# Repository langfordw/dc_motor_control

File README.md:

# dc_motor_control
microcode for control of DC motors

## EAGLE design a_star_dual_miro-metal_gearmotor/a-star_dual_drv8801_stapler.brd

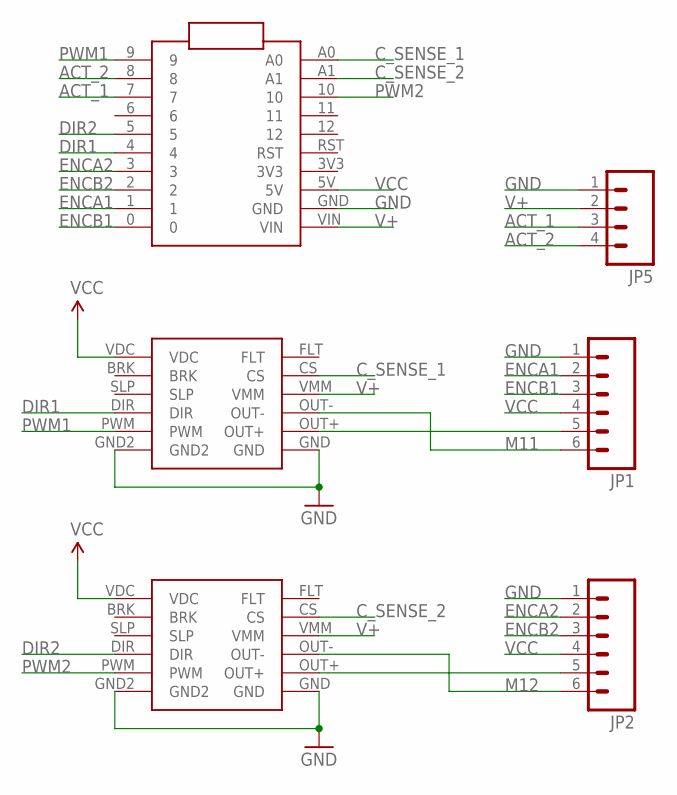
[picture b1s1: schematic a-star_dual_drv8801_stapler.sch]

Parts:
JP1, JP2: M06POLAR; MOLEX-1X6
JP5: M04POLAR; MOLEX-1X4
U$1, U$3: POLOLU_DRV8801_CARRIER
U$2: POLOLU_A-STAR-MICRO

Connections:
ACT_1: JP5.3, U$2.7
ACT_2: JP5.4, U$2.8
C_SENSE_1: U$1.CS, U$2.A0
C_SENSE_2: U$2.A1, U$3.CS
DIR1: U$1.DIR, U$2.4
DIR2: U$2.5, U$3.DIR
ENCA1: JP1.2, U$2.1
ENCA2: JP2.2, U$2.3
ENCB1: JP1.3, U$2.0
ENCB2: JP2.3, U$2.2
GND: JP1.1, JP2.1, JP5.1, U$1.GND, U$1.GND2, U$2.GND, U$3.GND, U$3.GND2
M11: JP1.6, U$1.OUT-
M12: JP2.6, U$3.OUT-
unnamed: JP2.5, U$3.OUT+
unnamed: JP1.5, U$1.OUT+
PWM1: U$1.PWM, U$2.9
PWM2: U$2.10, U$3.PWM
V+: JP5.2, U$1.VMM, U$2.VIN, U$3.VMM
VCC: JP1.4, JP2.4, U$1.VDC, U$2.5V, U$3.VDC

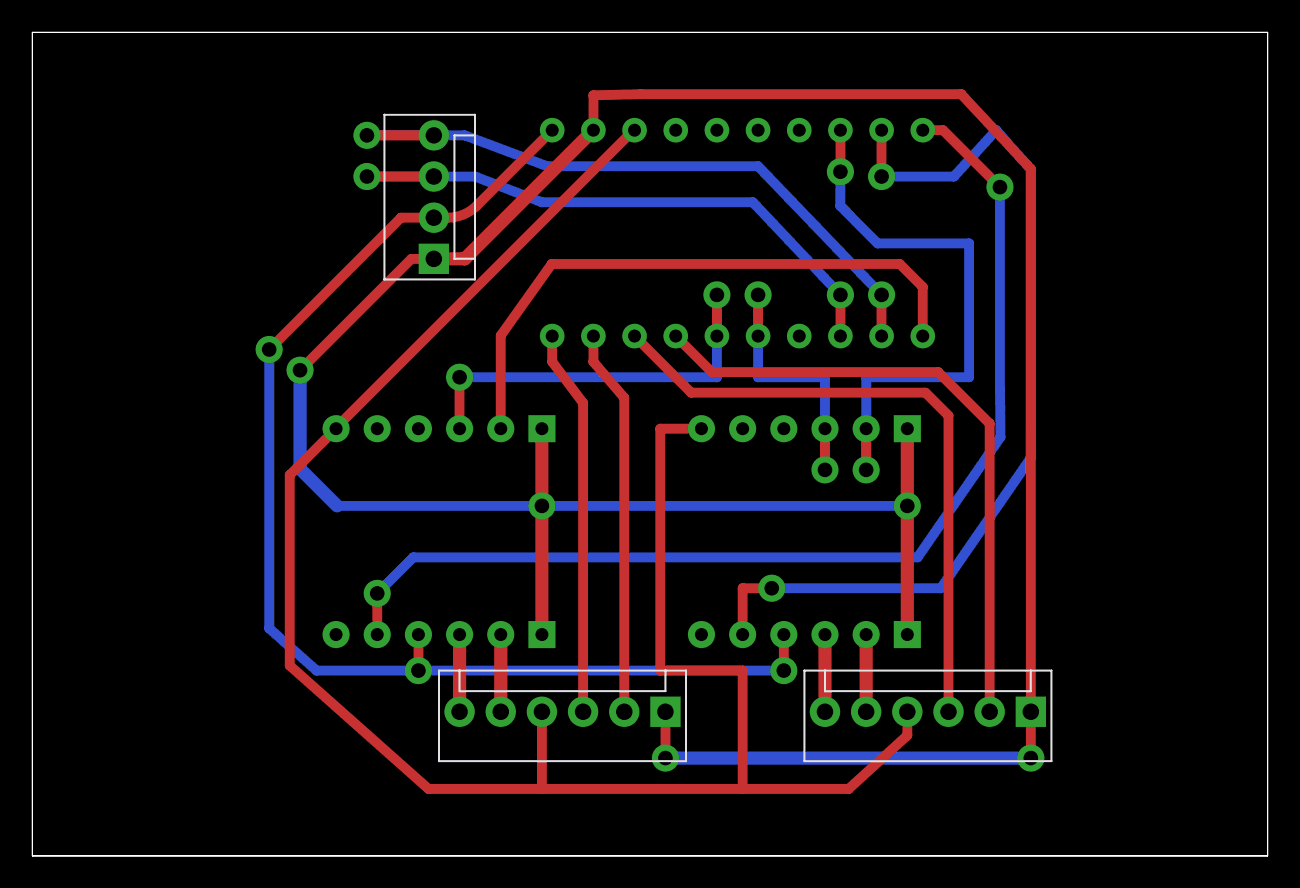
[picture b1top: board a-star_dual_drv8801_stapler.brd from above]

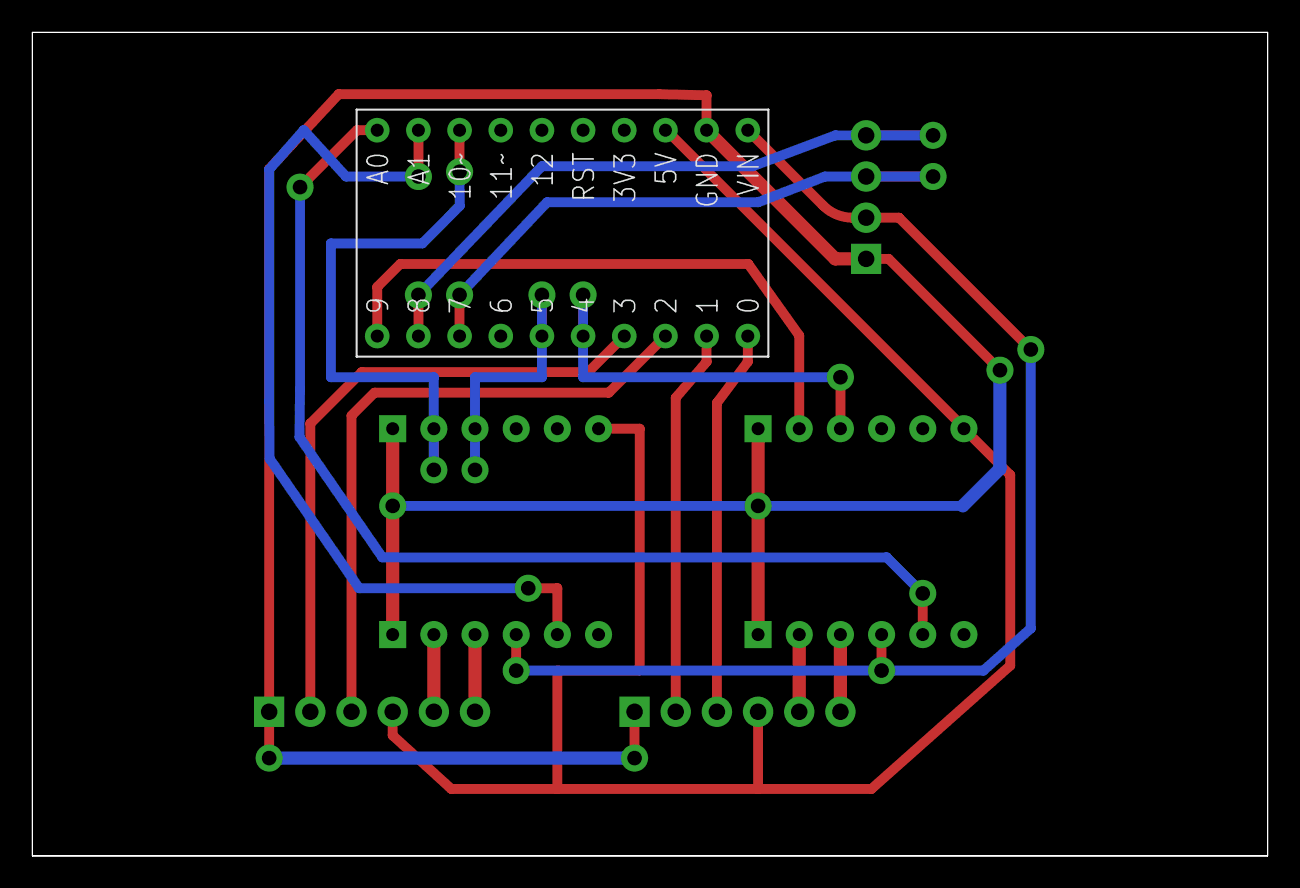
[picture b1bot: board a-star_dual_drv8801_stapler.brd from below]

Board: 2 copper layers, 76.2 x 50.8 mm, 6 parts (3 on the bottom side), 19 nets.

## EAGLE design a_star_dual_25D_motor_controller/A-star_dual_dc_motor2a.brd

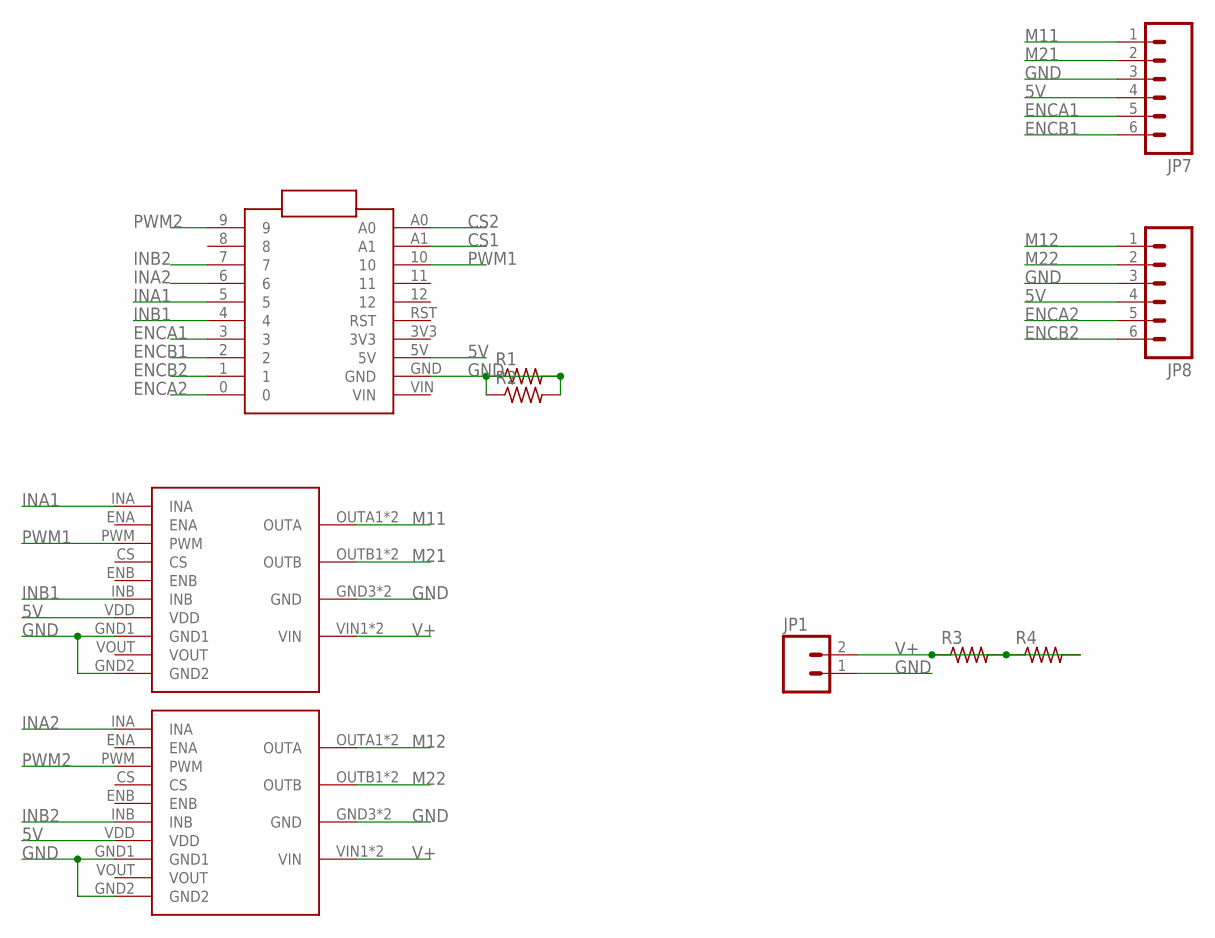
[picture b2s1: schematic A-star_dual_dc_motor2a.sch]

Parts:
ALL_PADS1, ALL_PADS2: POLOLU_VNH5019_CARRIER; VNH5019_CARRIER
JP1: M023.5MM; SCREWTERMINAL-3.5MM-2
JP7, JP8: M06SIP; 1X06
R1, R2, R3, R4: RES-US1206FAB; R1206FAB
U$1: POLOLU_A-STAR-MICRO

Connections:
5V: ALL_PADS1.VDD, ALL_PADS2.VDD, JP7.4, JP8.4, U$1.5V
CS1: U$1.A1
CS2: U$1.A0
ENCA1: JP7.5, U$1.3
ENCA2: JP8.5, U$1.0
ENCB1: JP7.6, U$1.2
ENCB2: JP8.6, U$1.1
GND: ALL_PADS1.GND1, ALL_PADS1.GND2, ALL_PADS1.GND3 (GND), ALL_PADS1.GND4 (GND), ALL_PADS2.GND1, ALL_PADS2.GND2, ALL_PADS2.GND3 (GND), ALL_PADS2.GND4 (GND), JP1.1, JP7.3, JP8.3, R1.1, R1.2, R2.1, R2.2, U$1.GND
INA1: ALL_PADS1.INA, U$1.5
INA2: ALL_PADS2.INA, U$1.6
INB1: ALL_PADS1.INB, U$1.4
INB2: ALL_PADS2.INB, U$1.7
M11: ALL_PADS1.OUTA1 (OUTA), ALL_PADS1.OUTA2 (OUTA), JP7.1
M12: ALL_PADS2.OUTA1 (OUTA), ALL_PADS2.OUTA2 (OUTA), JP8.1
M21: ALL_PADS1.OUTB1 (OUTB), ALL_PADS1.OUTB2 (OUTB), JP7.2
M22: ALL_PADS2.OUTB1 (OUTB), ALL_PADS2.OUTB2 (OUTB), JP8.2
PWM1: ALL_PADS1.PWM, U$1.10
PWM2: ALL_PADS2.PWM, U$1.9
V+: ALL_PADS1.VIN1 (VIN), ALL_PADS1.VIN2 (VIN), ALL_PADS2.VIN1 (VIN), ALL_PADS2.VIN2 (VIN), JP1.2, R3.1, R3.2, R4.1, R4.2

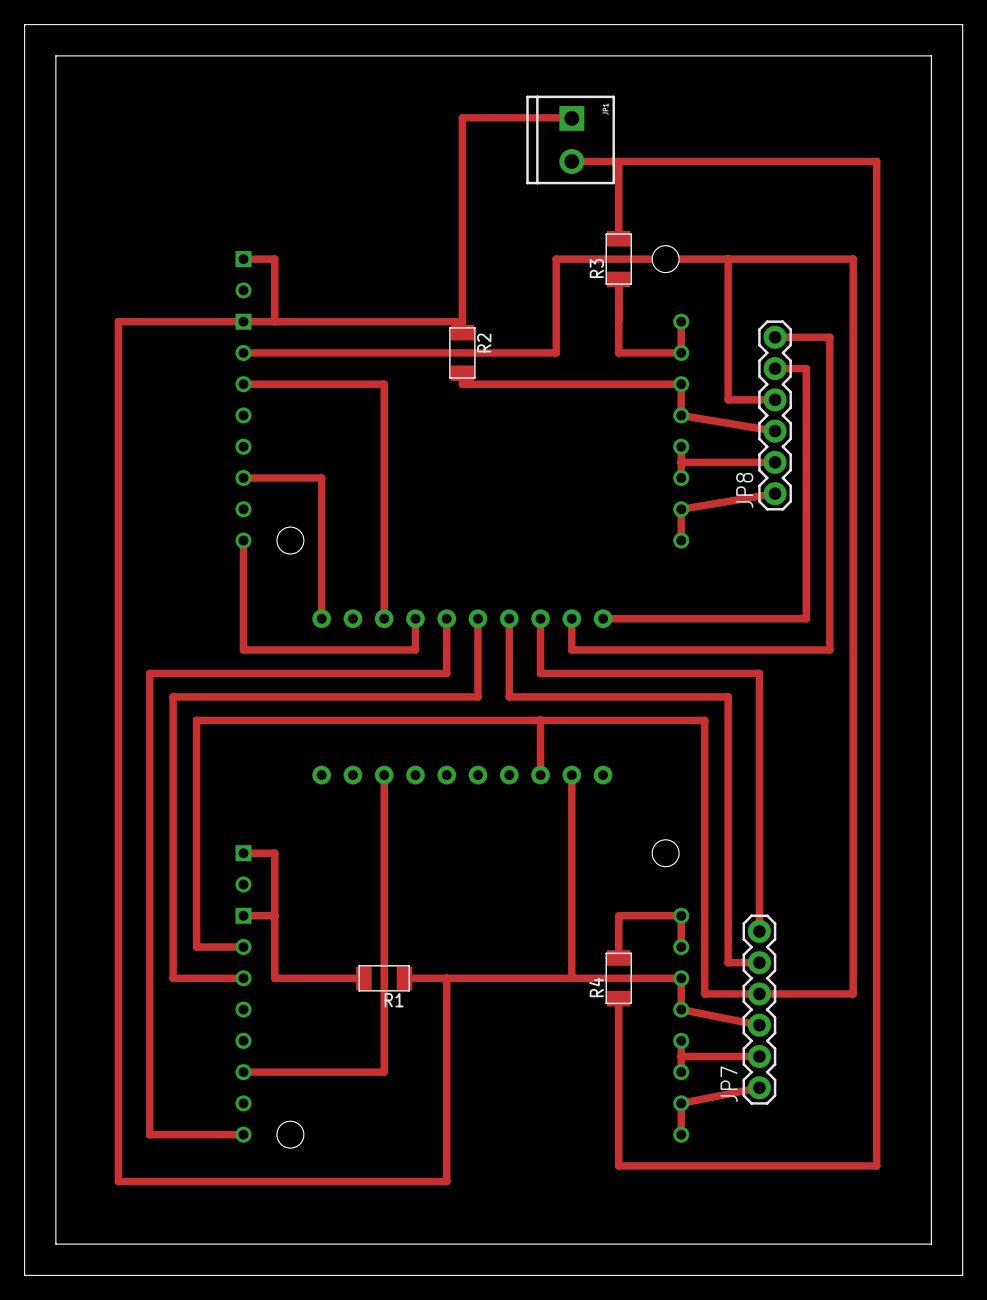
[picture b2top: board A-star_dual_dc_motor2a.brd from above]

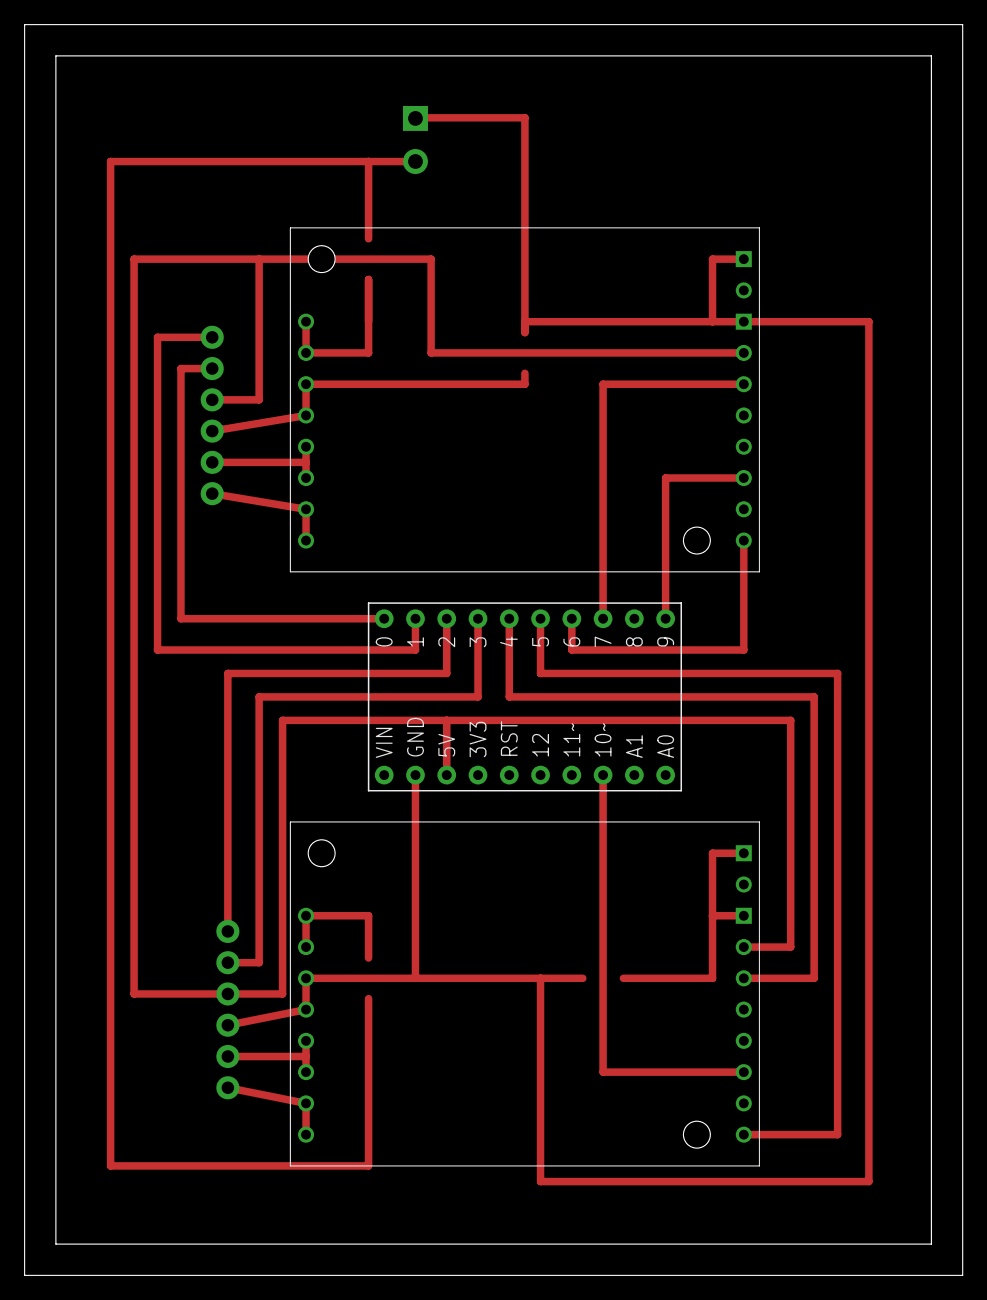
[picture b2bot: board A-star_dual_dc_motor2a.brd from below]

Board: 2 copper layers, 76.2 x 101.6 mm, 10 parts (3 on the bottom side), 17 nets.

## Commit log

2015-03-29 init repo with old code
2015-03-29 incorporating amanda's structure
2015-03-31 updating
2015-03-31 working drive, position, velocity measurement
2015-03-31 velocity and position control
2015-03-31 added dpos method of velocity measurement
2015-03-31 cleanup
2015-04-01 dc as stepper working
2015-04-02 gain scheduling test
2015-04-02 small change
2015-04-02 smaller change
2015-04-02 test
2015-04-04 small change to master
2015-04-04 adding pcbs
2015-04-14 added force control for wire tension gauge
2015-04-14 cleaned up
2015-06-21 modifying circuit for dual stapler control
2015-06-21 modifying for dual stapler
2015-06-21 copied code for micro motor
2015-06-23 stapler encoders working
2015-06-23 current control working for motor1
2015-06-23 moving between positions working for motor1
2015-06-23 both staplers working with new stapler class
2015-06-26 triggering from tinyg
2015-06-30 debugging strange drifting and ramping behavior of left stapler
2015-07-01 added push mode to combat drift... may still be an issue
2015-08-14 dialed in dual head
